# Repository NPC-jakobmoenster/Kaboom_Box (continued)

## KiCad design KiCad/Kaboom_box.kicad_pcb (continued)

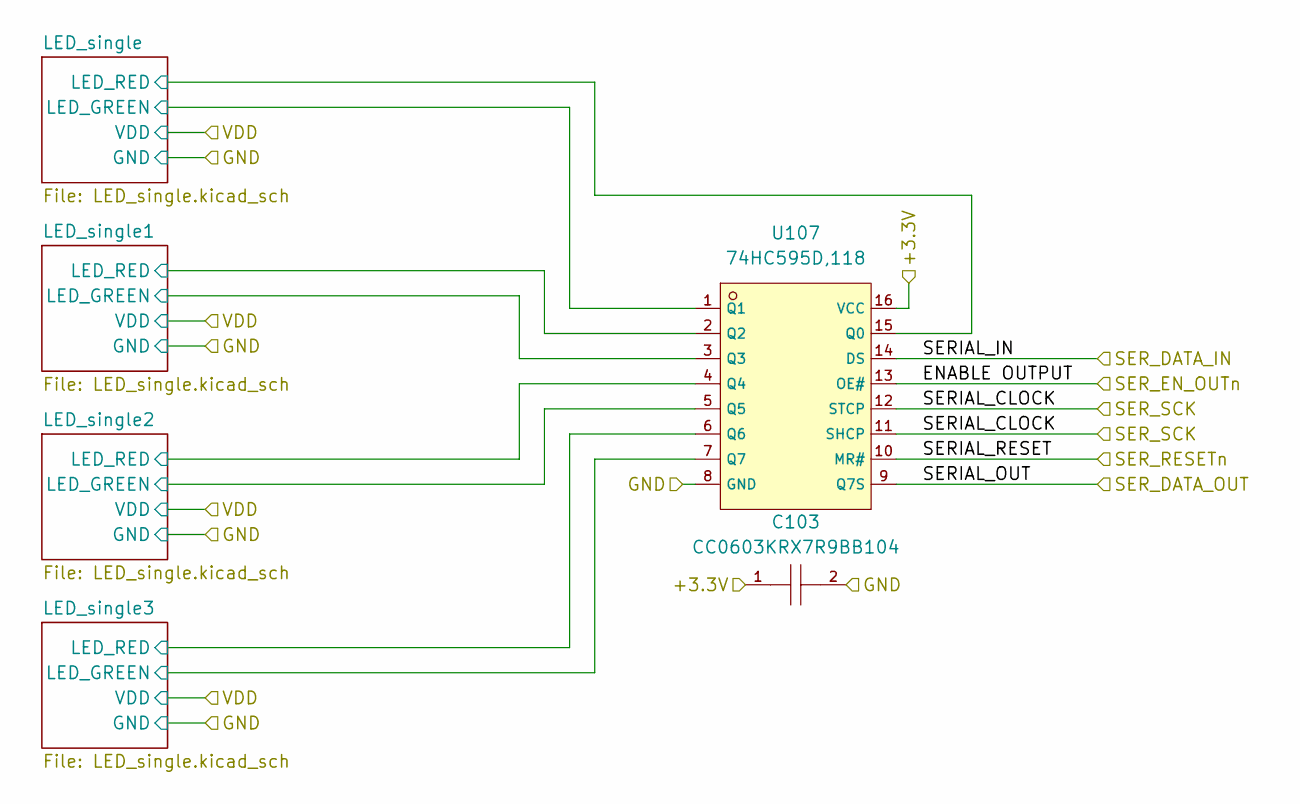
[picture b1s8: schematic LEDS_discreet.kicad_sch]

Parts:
C103: CC0603KRX7R9BB104; C0603; LCSC C14663
U107: 74HC595D,118; SOIC-16_L9.9-W3.9-P1.27-LS6.0-BL; LCSC C5947

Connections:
/Bottom/+3.3V: C103.1, U107.16 (VCC); also elsewhere on the board
/Bottom/LEDs_Bottom/LEDS_discreet/LED_single1/LED_GREEN: U107.3 (Q3); also elsewhere on the board
/Bottom/LEDs_Bottom/LEDS_discreet/LED_single1/LED_RED: U107.2 (Q2); also elsewhere on the board
/Bottom/LEDs_Bottom/LEDS_discreet/LED_single2/LED_GREEN: U107.5 (Q5); also elsewhere on the board
/Bottom/LEDs_Bottom/LEDS_discreet/LED_single2/LED_RED: U107.4 (Q4); also elsewhere on the board
/Bottom/LEDs_Bottom/LEDS_discreet/LED_single3/LED_GREEN: U107.7 (Q7); also elsewhere on the board
/Bottom/LEDs_Bottom/LEDS_discreet/LED_single3/LED_RED: U107.6 (Q6); also elsewhere on the board
/Bottom/LEDs_Bottom/LEDS_discreet/LED_single/LED_GREEN: U107.1 (Q1); also elsewhere on the board
/Bottom/LEDs_Bottom/LEDS_discreet/LED_single/LED_RED: U107.15 (Q0); also elsewhere on the board
/Bottom/LEDs_Bottom/LEDS_discreet/SERIAL_RESET: U107.10 (MR#); also elsewhere on the board
/Bottom/LEDs_Bottom/SER_DATA_OUT_1: U107.9 (Q7S); also elsewhere on the board
/Bottom/SOFTSPI_MOSI: U107.14 (DS); also elsewhere on the board
/SOFTSPI_CLK_BOT: U107.11 (SHCP), U107.12 (STCP); also elsewhere on the board
/SOFTSPI_CSn_BOT: U107.13 (OE#); also elsewhere on the board
GND: C103.2, U107.8 (GND); also elsewhere on the board

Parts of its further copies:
C116, C117, C118, C119, C120, C121, C122, C123, C124, C125, C126, C127, C128, C129, C130: CC0603KRX7R9BB104; C0603; LCSC C14663
U127, U129, U140, U151, U162, U175, U184, U193, U196, U205, U221, U230, U239, U248, U257: 74HC595D,118; SOIC-16_L9.9-W3.9-P1.27-LS6.0-BL; LCSC C5947

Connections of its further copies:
/Bottom/+3.3V: C117.1, C119.1, C121.1, C124.1, C126.1, C128.1, C130.1, U140.16 (VCC), U162.16 (VCC), U184.16 (VCC), U205.16 (VCC), U221.16 (VCC), U239.16 (VCC), U257.16 (VCC); also elsewhere on the board
/Bottom/LEDs_Bottom/LEDS_discreet2/LED_single1/LED_GREEN: U184.3 (Q3); also elsewhere on the board
/Bottom/LEDs_Bottom/LEDS_discreet2/LED_single1/LED_RED: U184.2 (Q2); also elsewhere on the board
/Bottom/LEDs_Bottom/LEDS_discreet2/LED_single2/LED_GREEN: U184.5 (Q5); also elsewhere on the board
/Bottom/LEDs_Bottom/LEDS_discreet2/LED_single2/LED_RED: U184.4 (Q4); also elsewhere on the board
/Bottom/LEDs_Bottom/LEDS_discreet2/LED_single3/LED_GREEN: U184.7 (Q7); also elsewhere on the board
/Bottom/LEDs_Bottom/LEDS_discreet2/LED_single3/LED_RED: U184.6 (Q6); also elsewhere on the board
/Bottom/LEDs_Bottom/LEDS_discreet2/LED_single/LED_GREEN: U184.1 (Q1); also elsewhere on the board
/Bottom/LEDs_Bottom/LEDS_discreet2/LED_single/LED_RED: U184.15 (Q0); also elsewhere on the board
/Bottom/LEDs_Bottom/LEDS_discreet3/LED_single1/LED_GREEN: U140.3 (Q3); also elsewhere on the board
/Bottom/LEDs_Bottom/LEDS_discreet3/LED_single1/LED_RED: U140.2 (Q2); also elsewhere on the board
/Bottom/LEDs_Bottom/LEDS_discreet3/LED_single2/LED_GREEN: U140.5 (Q5); also elsewhere on the board
/Bottom/LEDs_Bottom/LEDS_discreet3/LED_single2/LED_RED: U140.4 (Q4); also elsewhere on the board
/Bottom/LEDs_Bottom/LEDS_discreet3/LED_single3/LED_GREEN: U140.7 (Q7); also elsewhere on the board
/Bottom/LEDs_Bottom/LEDS_discreet3/LED_single3/LED_RED: U140.6 (Q6); also elsewhere on the board
/Bottom/LEDs_Bottom/LEDS_discreet3/LED_single/LED_GREEN: U140.1 (Q1); also elsewhere on the board
/Bottom/LEDs_Bottom/LEDS_discreet3/LED_single/LED_RED: U140.15 (Q0); also elsewhere on the board
/Bottom/LEDs_Bottom/LEDS_discreet4/LED_single1/LED_GREEN: U162.3 (Q3); also elsewhere on the board
/Bottom/LEDs_Bottom/LEDS_discreet4/LED_single1/LED_RED: U162.2 (Q2); also elsewhere on the board
/Bottom/LEDs_Bottom/LEDS_discreet4/LED_single2/LED_GREEN: U162.5 (Q5); also elsewhere on the board
/Bottom/LEDs_Bottom/LEDS_discreet4/LED_single2/LED_RED: U162.4 (Q4); also elsewhere on the board
/Bottom/LEDs_Bottom/LEDS_discreet4/LED_single3/LED_GREEN: U162.7 (Q7); also elsewhere on the board
/Bottom/LEDs_Bottom/LEDS_discreet4/LED_single3/LED_RED: U162.6 (Q6); also elsewhere on the board
/Bottom/LEDs_Bottom/LEDS_discreet4/LED_single/LED_GREEN: U162.1 (Q1); also elsewhere on the board
/Bottom/LEDs_Bottom/LEDS_discreet4/LED_single/LED_RED: U162.15 (Q0); also elsewhere on the board
/Bottom/LEDs_Bottom/LEDS_discreet5/LED_single1/LED_GREEN: U205.3 (Q3); also elsewhere on the board
/Bottom/LEDs_Bottom/LEDS_discreet5/LED_single1/LED_RED: U205.2 (Q2); also elsewhere on the board
/Bottom/LEDs_Bottom/LEDS_discreet5/LED_single2/LED_GREEN: U205.5 (Q5); also elsewhere on the board
/Bottom/LEDs_Bottom/LEDS_discreet5/LED_single2/LED_RED: U205.4 (Q4); also elsewhere on the board
/Bottom/LEDs_Bottom/LEDS_discreet5/LED_single3/LED_GREEN: U205.7 (Q7); also elsewhere on the board
/Bottom/LEDs_Bottom/LEDS_discreet5/LED_single3/LED_RED: U205.6 (Q6); also elsewhere on the board
/Bottom/LEDs_Bottom/LEDS_discreet5/LED_single/LED_GREEN: U205.1 (Q1); also elsewhere on the board
/Bottom/LEDs_Bottom/LEDS_discreet5/LED_single/LED_RED: U205.15 (Q0); also elsewhere on the board
/Bottom/LEDs_Bottom/LEDS_discreet6/LED_single1/LED_GREEN: U221.3 (Q3); also elsewhere on the board
/Bottom/LEDs_Bottom/LEDS_discreet6/LED_single1/LED_RED: U221.2 (Q2); also elsewhere on the board
/Bottom/LEDs_Bottom/LEDS_discreet6/LED_single2/LED_GREEN: U221.5 (Q5); also elsewhere on the board
/Bottom/LEDs_Bottom/LEDS_discreet6/LED_single2/LED_RED: U221.4 (Q4); also elsewhere on the board
/Bottom/LEDs_Bottom/LEDS_discreet6/LED_single3/LED_GREEN: U221.7 (Q7); also elsewhere on the board
/Bottom/LEDs_Bottom/LEDS_discreet6/LED_single3/LED_RED: U221.6 (Q6); also elsewhere on the board
/Bottom/LEDs_Bottom/LEDS_discreet6/LED_single/LED_GREEN: U221.1 (Q1); also elsewhere on the board
/Bottom/LEDs_Bottom/LEDS_discreet6/LED_single/LED_RED: U221.15 (Q0); also elsewhere on the board
/Bottom/LEDs_Bottom/LEDS_discreet7/LED_single1/LED_GREEN: U239.3 (Q3); also elsewhere on the board
/Bottom/LEDs_Bottom/LEDS_discreet7/LED_single1/LED_RED: U239.2 (Q2); also elsewhere on the board
/Bottom/LEDs_Bottom/LEDS_discreet7/LED_single2/LED_GREEN: U239.5 (Q5); also elsewhere on the board
/Bottom/LEDs_Bottom/LEDS_discreet7/LED_single2/LED_RED: U239.4 (Q4); also elsewhere on the board
/Bottom/LEDs_Bottom/LEDS_discreet7/LED_single3/LED_GREEN: U239.7 (Q7); also elsewhere on the board
/Bottom/LEDs_Bottom/LEDS_discreet7/LED_single3/LED_RED: U239.6 (Q6); also elsewhere on the board
/Bottom/LEDs_Bottom/LEDS_discreet7/LED_single/LED_GREEN: U239.1 (Q1); also elsewhere on the board
/Bottom/LEDs_Bottom/LEDS_discreet7/LED_single/LED_RED: U239.15 (Q0); also elsewhere on the board
/Bottom/LEDs_Bottom/LEDS_discreet8/LED_single1/LED_GREEN: U257.3 (Q3); also elsewhere on the board
/Bottom/LEDs_Bottom/LEDS_discreet8/LED_single1/LED_RED: U257.2 (Q2); also elsewhere on the board
/Bottom/LEDs_Bottom/LEDS_discreet8/LED_single2/LED_GREEN: U257.5 (Q5); also elsewhere on the board
/Bottom/LEDs_Bottom/LEDS_discreet8/LED_single2/LED_RED: U257.4 (Q4); also elsewhere on the board
/Bottom/LEDs_Bottom/LEDS_discreet8/LED_single3/LED_GREEN: U257.7 (Q7); also elsewhere on the board
/Bottom/LEDs_Bottom/LEDS_discreet8/LED_single3/LED_RED: U257.6 (Q6); also elsewhere on the board
/Bottom/LEDs_Bottom/LEDS_discreet8/LED_single/LED_GREEN: U257.1 (Q1); also elsewhere on the board
/Bottom/LEDs_Bottom/LEDS_discreet8/LED_single/LED_RED: U257.15 (Q0); also elsewhere on the board
/Bottom/LEDs_Bottom/LEDS_discreet/SERIAL_RESET: U140.10 (MR#), U162.10 (MR#), U184.10 (MR#), U205.10 (MR#), U221.10 (MR#), U239.10 (MR#), U257.10 (MR#); also elsewhere on the board
/Bottom/LEDs_Bottom/SER_DATA_OUT_1: U184.14 (DS); also elsewhere on the board
/Bottom/LEDs_Bottom/SER_DATA_OUT_2: U140.14 (DS), U184.9 (Q7S)
/Bottom/LEDs_Bottom/SER_DATA_OUT_3: U140.9 (Q7S), U162.14 (DS)
/Bottom/LEDs_Bottom/SER_DATA_OUT_4: U162.9 (Q7S), U205.14 (DS)
/Bottom/LEDs_Bottom/SER_DATA_OUT_5: U205.9 (Q7S), U221.14 (DS)
/Bottom/LEDs_Bottom/SER_DATA_OUT_6: U221.9 (Q7S), U239.14 (DS)
/Bottom/LEDs_Bottom/SER_DATA_OUT_7: U239.9 (Q7S), U257.14 (DS)
/SER_DATA_IN_0: U193.14 (DS); also elsewhere on the board
/SER_DATA_OUT_8_BOT: U257.9 (Q7S); also elsewhere on the board
/SOFTSPI_CLK_BOT: U140.11 (SHCP), U140.12 (STCP), U162.11 (SHCP), U162.12 (STCP), U184.11 (SHCP), U184.12 (STCP), U205.11 (SHCP), U205.12 (STCP), U221.11 (SHCP), U221.12 (STCP), U239.11 (SHCP), U239.12 (STCP), U257.11 (SHCP), U257.12 (STCP); also elsewhere on the board
/SOFTSPI_CLK_LID: U127.11 (SHCP), U127.12 (STCP), U129.11 (SHCP), U129.12 (STCP), U151.11 (SHCP), U151.12 (STCP), U175.11 (SHCP), U175.12 (STCP), U193.11 (SHCP), U193.12 (STCP), U196.11 (SHCP), U196.12 (STCP), U230.11 (SHCP), U230.12 (STCP), U248.11 (SHCP), U248.12 (STCP); also elsewhere on the board
/SOFTSPI_CSn_BOT: U140.13 (OE#), U162.13 (OE#), U184.13 (OE#), U205.13 (OE#), U221.13 (OE#), U239.13 (OE#), U257.13 (OE#); also elsewhere on the board
/SOFTSPI_CSn_LID: U127.13 (OE#), U129.13 (OE#), U151.13 (OE#), U175.13 (OE#), U193.13 (OE#), U196.13 (OE#), U230.13 (OE#), U248.13 (OE#); also elsewhere on the board
/SOFTSPI_RST_LID: U127.10 (MR#), U129.10 (MR#), U151.10 (MR#), U175.10 (MR#), U193.10 (MR#), U196.10 (MR#), U230.10 (MR#), U248.10 (MR#); also elsewhere on the board
/Top/+3.3V_LEDS: C116.1, C118.1, C120.1, C122.1, C123.1, C125.1, C127.1, C129.1, U127.16 (VCC), U129.16 (VCC), U151.16 (VCC), U175.16 (VCC), U193.16 (VCC), U196.16 (VCC), U230.16 (VCC), U248.16 (VCC); also elsewhere on the board
/Top/GND: C116.2, C118.2, C120.2, C122.2, C123.2, C125.2, C127.2, C129.2, U127.8 (GND), U129.8 (GND), U151.8 (GND), U175.8 (GND), U193.8 (GND), U196.8 (GND), U230.8 (GND), U248.8 (GND); also elsewhere on the board
/Top/LEDs_Bottom/LEDS_discreet2/LED_single1/LED_GREEN: U175.3 (Q3); also elsewhere on the board
/Top/LEDs_Bottom/LEDS_discreet2/LED_single1/LED_RED: U175.2 (Q2); also elsewhere on the board
/Top/LEDs_Bottom/LEDS_discreet2/LED_single2/LED_GREEN: U175.5 (Q5); also elsewhere on the board
/Top/LEDs_Bottom/LEDS_discreet2/LED_single2/LED_RED: U175.4 (Q4); also elsewhere on the board
/Top/LEDs_Bottom/LEDS_discreet2/LED_single3/LED_GREEN: U175.7 (Q7); also elsewhere on the board
/Top/LEDs_Bottom/LEDS_discreet2/LED_single3/LED_RED: U175.6 (Q6); also elsewhere on the board
/Top/LEDs_Bottom/LEDS_discreet2/LED_single/LED_GREEN: U175.1 (Q1); also elsewhere on the board
/Top/LEDs_Bottom/LEDS_discreet2/LED_single/LED_RED: U175.15 (Q0); also elsewhere on the board
/Top/LEDs_Bottom/LEDS_discreet3/LED_single1/LED_GREEN: U129.3 (Q3); also elsewhere on the board
/Top/LEDs_Bottom/LEDS_discreet3/LED_single1/LED_RED: U129.2 (Q2); also elsewhere on the board
/Top/LEDs_Bottom/LEDS_discreet3/LED_single2/LED_GREEN: U129.5 (Q5); also elsewhere on the board
/Top/LEDs_Bottom/LEDS_discreet3/LED_single2/LED_RED: U129.4 (Q4); also elsewhere on the board
/Top/LEDs_Bottom/LEDS_discreet3/LED_single3/LED_GREEN: U129.7 (Q7); also elsewhere on the board
/Top/LEDs_Bottom/LEDS_discreet3/LED_single3/LED_RED: U129.6 (Q6); also elsewhere on the board
/Top/LEDs_Bottom/LEDS_discreet3/LED_single/LED_GREEN: U129.1 (Q1); also elsewhere on the board
/Top/LEDs_Bottom/LEDS_discreet3/LED_single/LED_RED: U129.15 (Q0); also elsewhere on the board
/Top/LEDs_Bottom/LEDS_discreet4/LED_single1/LED_GREEN: U151.3 (Q3); also elsewhere on the board
/Top/LEDs_Bottom/LEDS_discreet4/LED_single1/LED_RED: U151.2 (Q2); also elsewhere on the board
/Top/LEDs_Bottom/LEDS_discreet4/LED_single2/LED_GREEN: U151.5 (Q5); also elsewhere on the board
/Top/LEDs_Bottom/LEDS_discreet4/LED_single2/LED_RED: U151.4 (Q4); also elsewhere on the board
/Top/LEDs_Bottom/LEDS_discreet4/LED_single3/LED_GREEN: U151.7 (Q7); also elsewhere on the board
/Top/LEDs_Bottom/LEDS_discreet4/LED_single3/LED_RED: U151.6 (Q6); also elsewhere on the board
/Top/LEDs_Bottom/LEDS_discreet4/LED_single/LED_GREEN: U151.1 (Q1); also elsewhere on the board
/Top/LEDs_Bottom/LEDS_discreet4/LED_single/LED_RED: U151.15 (Q0); also elsewhere on the board
/Top/LEDs_Bottom/LEDS_discreet5/LED_single1/LED_GREEN: U196.3 (Q3); also elsewhere on the board
/Top/LEDs_Bottom/LEDS_discreet5/LED_single1/LED_RED: U196.2 (Q2); also elsewhere on the board
/Top/LEDs_Bottom/LEDS_discreet5/LED_single2/LED_GREEN: U196.5 (Q5); also elsewhere on the board
/Top/LEDs_Bottom/LEDS_discreet5/LED_single2/LED_RED: U196.4 (Q4); also elsewhere on the board
/Top/LEDs_Bottom/LEDS_discreet5/LED_single3/LED_GREEN: U196.7 (Q7); also elsewhere on the board
/Top/LEDs_Bottom/LEDS_discreet5/LED_single3/LED_RED: U196.6 (Q6); also elsewhere on the board
/Top/LEDs_Bottom/LEDS_discreet5/LED_single/LED_GREEN: U196.1 (Q1); also elsewhere on the board
/Top/LEDs_Bottom/LEDS_discreet5/LED_single/LED_RED: U196.15 (Q0); also elsewhere on the board
/Top/LEDs_Bottom/LEDS_discreet6/LED_single1/LED_GREEN: U127.3 (Q3); also elsewhere on the board
/Top/LEDs_Bottom/LEDS_discreet6/LED_single1/LED_RED: U127.2 (Q2); also elsewhere on the board
/Top/LEDs_Bottom/LEDS_discreet6/LED_single2/LED_GREEN: U127.5 (Q5); also elsewhere on the board
/Top/LEDs_Bottom/LEDS_discreet6/LED_single2/LED_RED: U127.4 (Q4); also elsewhere on the board
/Top/LEDs_Bottom/LEDS_discreet6/LED_single3/LED_GREEN: U127.7 (Q7); also elsewhere on the board
/Top/LEDs_Bottom/LEDS_discreet6/LED_single3/LED_RED: U127.6 (Q6); also elsewhere on the board
/Top/LEDs_Bottom/LEDS_discreet6/LED_single/LED_GREEN: U127.1 (Q1); also elsewhere on the board
/Top/LEDs_Bottom/LEDS_discreet6/LED_single/LED_RED: U127.15 (Q0); also elsewhere on the board
/Top/LEDs_Bottom/LEDS_discreet7/LED_single1/LED_GREEN: U230.3 (Q3); also elsewhere on the board
/Top/LEDs_Bottom/LEDS_discreet7/LED_single1/LED_RED: U230.2 (Q2); also elsewhere on the board
/Top/LEDs_Bottom/LEDS_discreet7/LED_single2/LED_GREEN: U230.5 (Q5); also elsewhere on the board
/Top/LEDs_Bottom/LEDS_discreet7/LED_single2/LED_RED: U230.4 (Q4); also elsewhere on the board
/Top/LEDs_Bottom/LEDS_discreet7/LED_single3/LED_GREEN: U230.7 (Q7); also elsewhere on the board
/Top/LEDs_Bottom/LEDS_discreet7/LED_single3/LED_RED: U230.6 (Q6); also elsewhere on the board
/Top/LEDs_Bottom/LEDS_discreet7/LED_single/LED_GREEN: U230.1 (Q1); also elsewhere on the board
/Top/LEDs_Bottom/LEDS_discreet7/LED_single/LED_RED: U230.15 (Q0); also elsewhere on the board
/Top/LEDs_Bottom/LEDS_discreet8/LED_single1/LED_GREEN: U248.3 (Q3); also elsewhere on the board
/Top/LEDs_Bottom/LEDS_discreet8/LED_single1/LED_RED: U248.2 (Q2); also elsewhere on the board
/Top/LEDs_Bottom/LEDS_discreet8/LED_single2/LED_GREEN: U248.5 (Q5); also elsewhere on the board
/Top/LEDs_Bottom/LEDS_discreet8/LED_single2/LED_RED: U248.4 (Q4); also elsewhere on the board
/Top/LEDs_Bottom/LEDS_discreet8/LED_single3/LED_GREEN: U248.7 (Q7); also elsewhere on the board
/Top/LEDs_Bottom/LEDS_discreet8/LED_single3/LED_RED: U248.6 (Q6); also elsewhere on the board
/Top/LEDs_Bottom/LEDS_discreet8/LED_single/LED_GREEN: U248.1 (Q1); also elsewhere on the board
/Top/LEDs_Bottom/LEDS_discreet8/LED_single/LED_RED: U248.15 (Q0); also elsewhere on the board
/Top/LEDs_Bottom/LEDS_discreet/LED_single1/LED_GREEN: U193.3 (Q3); also elsewhere on the board
/Top/LEDs_Bottom/LEDS_discreet/LED_single1/LED_RED: U193.2 (Q2); also elsewhere on the board
/Top/LEDs_Bottom/LEDS_discreet/LED_single2/LED_GREEN: U193.5 (Q5); also elsewhere on the board
/Top/LEDs_Bottom/LEDS_discreet/LED_single2/LED_RED: U193.4 (Q4); also elsewhere on the board
/Top/LEDs_Bottom/LEDS_discreet/LED_single3/LED_GREEN: U193.7 (Q7); also elsewhere on the board
/Top/LEDs_Bottom/LEDS_discreet/LED_single3/LED_RED: U193.6 (Q6); also elsewhere on the board
/Top/LEDs_Bottom/LEDS_discreet/LED_single/LED_GREEN: U193.1 (Q1); also elsewhere on the board
/Top/LEDs_Bottom/LEDS_discreet/LED_single/LED_RED: U193.15 (Q0); also elsewhere on the board
/Top/LEDs_Bottom/SER_DATA_OUT_1: U175.14 (DS), U193.9 (Q7S)
/Top/LEDs_Bottom/SER_DATA_OUT_2: U129.14 (DS), U175.9 (Q7S)
/Top/LEDs_Bottom/SER_DATA_OUT_3: U129.9 (Q7S), U151.14 (DS)
/Top/LEDs_Bottom/SER_DATA_OUT_4: U151.9 (Q7S), U196.14 (DS)
/Top/LEDs_Bottom/SER_DATA_OUT_5: U127.14 (DS), U196.9 (Q7S)
/Top/LEDs_Bottom/SER_DATA_OUT_6: U127.9 (Q7S), U230.14 (DS)
/Top/LEDs_Bottom/SER_DATA_OUT_7: U230.9 (Q7S), U248.14 (DS)
/Top/LEDs_Bottom/SER_DATA_OUT_8: U248.9 (Q7S)
GND: C117.2, C119.2, C121.2, C124.2, C126.2, C128.2, C130.2, U140.8 (GND), U162.8 (GND), U184.8 (GND), U205.8 (GND), U221.8 (GND), U239.8 (GND), U257.8 (GND); also elsewhere on the board
